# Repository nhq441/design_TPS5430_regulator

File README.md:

# TPS5430 Dual Buck Converter Module

---

## 📖 Introduction

This project presents the design and implementation of a **DC/DC Buck Converter (Step-Down) Power Supply Module** using **two Texas Instruments TPS5430** ICs. The module accepts a wide input voltage range of **14.4V – 25.2V** and delivers multiple regulated output rails suitable for embedded systems and microcontroller-based applications.

Key features include a **3-mode adjustable main output (VP)**, dual auxiliary LDO rails, a **Power Good LED indicator**, and a **configurable overcurrent protection** threshold set via a shunt resistor.

**Course:** Power Electronics and Applications — Course Code: `BTL_DTCSUD`

---

## 🖼️ PCB Images

### Schematic Overview
> 📷 *[Insert full schematic image here]*

---

### PCB Layout — Top Layer

---

### PCB Layout — Bottom Layer

---

### 3D Render

---

### Assembled Board
> 📷 *[Insert photo of the soldered/assembled board here]*

---

## ⚙️ Technical Specifications

| Parameter | Value | Notes |
| :--- | :--- | :--- |
| **Input Voltage ($V_{IN}$)** | 14.4V – 25.2V | Recommended operating range |
| **Main Output VP** | **5V / 12V / 3.3–12V** | 3 selectable modes |
| **VP Output Current** | Max **3A** | High-efficiency switching mode |
| **Auxiliary Output 1** | **5V** | Via LDO, for logic circuits |
| **Auxiliary Output 2** | **3.3V** | Via LDO, for MCUs (ESP32, STM32, etc.) |
| **Switching Frequency** | 500 kHz | Fixed internal oscillator |
| **Buck IC** | 2× TPS5430 | Texas Instruments |
| **Overcurrent Protection** | Configurable | Set via shunt resistor value |
| **Power Good Indicator** | LED (VP rail) | Signals stable output on VP |

---

## 🛠️ Design Details

### 1. Dual TPS5430 Architecture

The module employs **two independent TPS5430 ICs**:
- **IC1:** Drives the main output rail **VP**, supporting 3 selectable voltage modes.
- **IC2:** *(Describe the role of the second IC here — e.g., secondary rail, redundancy, or higher current capacity)*

### 2. Three-Mode Main Output (VP)

The VP rail supports three operating modes, selected via a switch or jumper:

| Mode | Output Voltage | Configuration |
| :---: | :---: | :--- |
| **Mode 1** | **5V** | Fixed feedback resistor network |
| **Mode 2** | **12V** | Fixed feedback resistor network |
| **Mode 3** | **3.3V – 12V** | Adjustable via potentiometer |

### 3. Feedback Network Calculation

The output voltage is set by a resistor divider ($R_1$, $R_2$) connected to the **VSENSE** pin, based on the internal reference $V_{ref} = 1.221V$:

$$V_{OUT} = V_{ref} \times \left(1 + \frac{R_1}{R_2}\right)$$

**With $R_1 = 10k\Omega$ (fixed):**

- **5V Mode:**

$$R_2 = \frac{R_1 \times V_{ref}}{V_{OUT} - V_{ref}} = \frac{10000 \times 1.221}{5.0 - 1.221} \approx 3.24k\Omega$$

- **12V Mode:**

$$R_2 = \frac{10000 \times 1.221}{12.0 - 1.221} \approx 1.13k\Omega$$

- **Variable Mode:** $R_2$ is replaced with a **5kΩ potentiometer in series with a 1kΩ fixed resistor**, allowing continuous adjustment from **3.3V to 12V**.

### 4. Auxiliary LDO Outputs (5V & 3.3V)

Both LDO regulators are cascaded from the **5V Buck output**, not directly from $V_{IN}$:
- **Reason:** Reduces the voltage drop across each LDO, minimizing power dissipation ($P_D = \Delta V \times I_{load}$).
- **Benefit:** Allows the use of compact packages (e.g., SOT-223) without thermal issues.

### 5. Power Good LED Indicator

A **Power Good LED** is connected to the VP rail. The LED lights up when VP reaches its target voltage, confirming stable regulation before connecting a load.

### 6. Configurable Overcurrent Protection

A **low-side shunt resistor** sets the overcurrent trip threshold. Changing the resistor value adjusts the protection level to match the target application's requirements. The sensing node is labeled **ISENSE** in the schematic.

---

## 📂 Project Structure

```text
BTL_DTCSUD/
├── docs/                       # Documentation & Report files
│   └── ...
├── Kicad/                      # Hardware Design Files
│   └── Buck_TPS5430/
│       ├── *.kicad_sch         # Schematic file
│       ├── *.kicad_pcb         # PCB Layout file
│       └── ...
├── reference/                  # Datasheets & Assignment requirements
│   └── ...
├── .gitignore
├── GIT_GUIDE
└── README.md
```

---

## 🚀 Getting Started

### Prerequisites
- **[KiCad EDA](https://www.kicad.org/)** — Version 9.0 or higher recommended
- **[Git](https://git-scm.com/)** — For version control

### Installation

**Option 1: Clone via Git (Recommended)**
```bash
git clone https://github.com/nhq441/design_TPS5430_regulator.git
```

**Option 2: Download ZIP**
1. Click the green **<> Code** button at the top right of this repository page.
2. Select **Download ZIP**.
3. Extract the `.zip` file to your working directory.

### Opening the Project
1. Launch **KiCad**.
2. Navigate to: `Kicad/Buck_TPS5430/`
3. Open: `Buck_TPS5430.kicad_pro`

---

## 🤝 Contributing

This project follows the **Gitflow Workflow**:

- **`main`**: Stable, verified designs only.
- **`develop`**: Primary integration branch for ongoing work.
- **`feature/*`**: Individual feature branches (e.g., `feature/Schematic`, `feature/PCB-Layout`).
  - Always branch from `develop` and merge back via Pull Request.

---

## 📄 License

This project is developed for **educational purposes** within the scope of the **Power Electronics and Applications** course.

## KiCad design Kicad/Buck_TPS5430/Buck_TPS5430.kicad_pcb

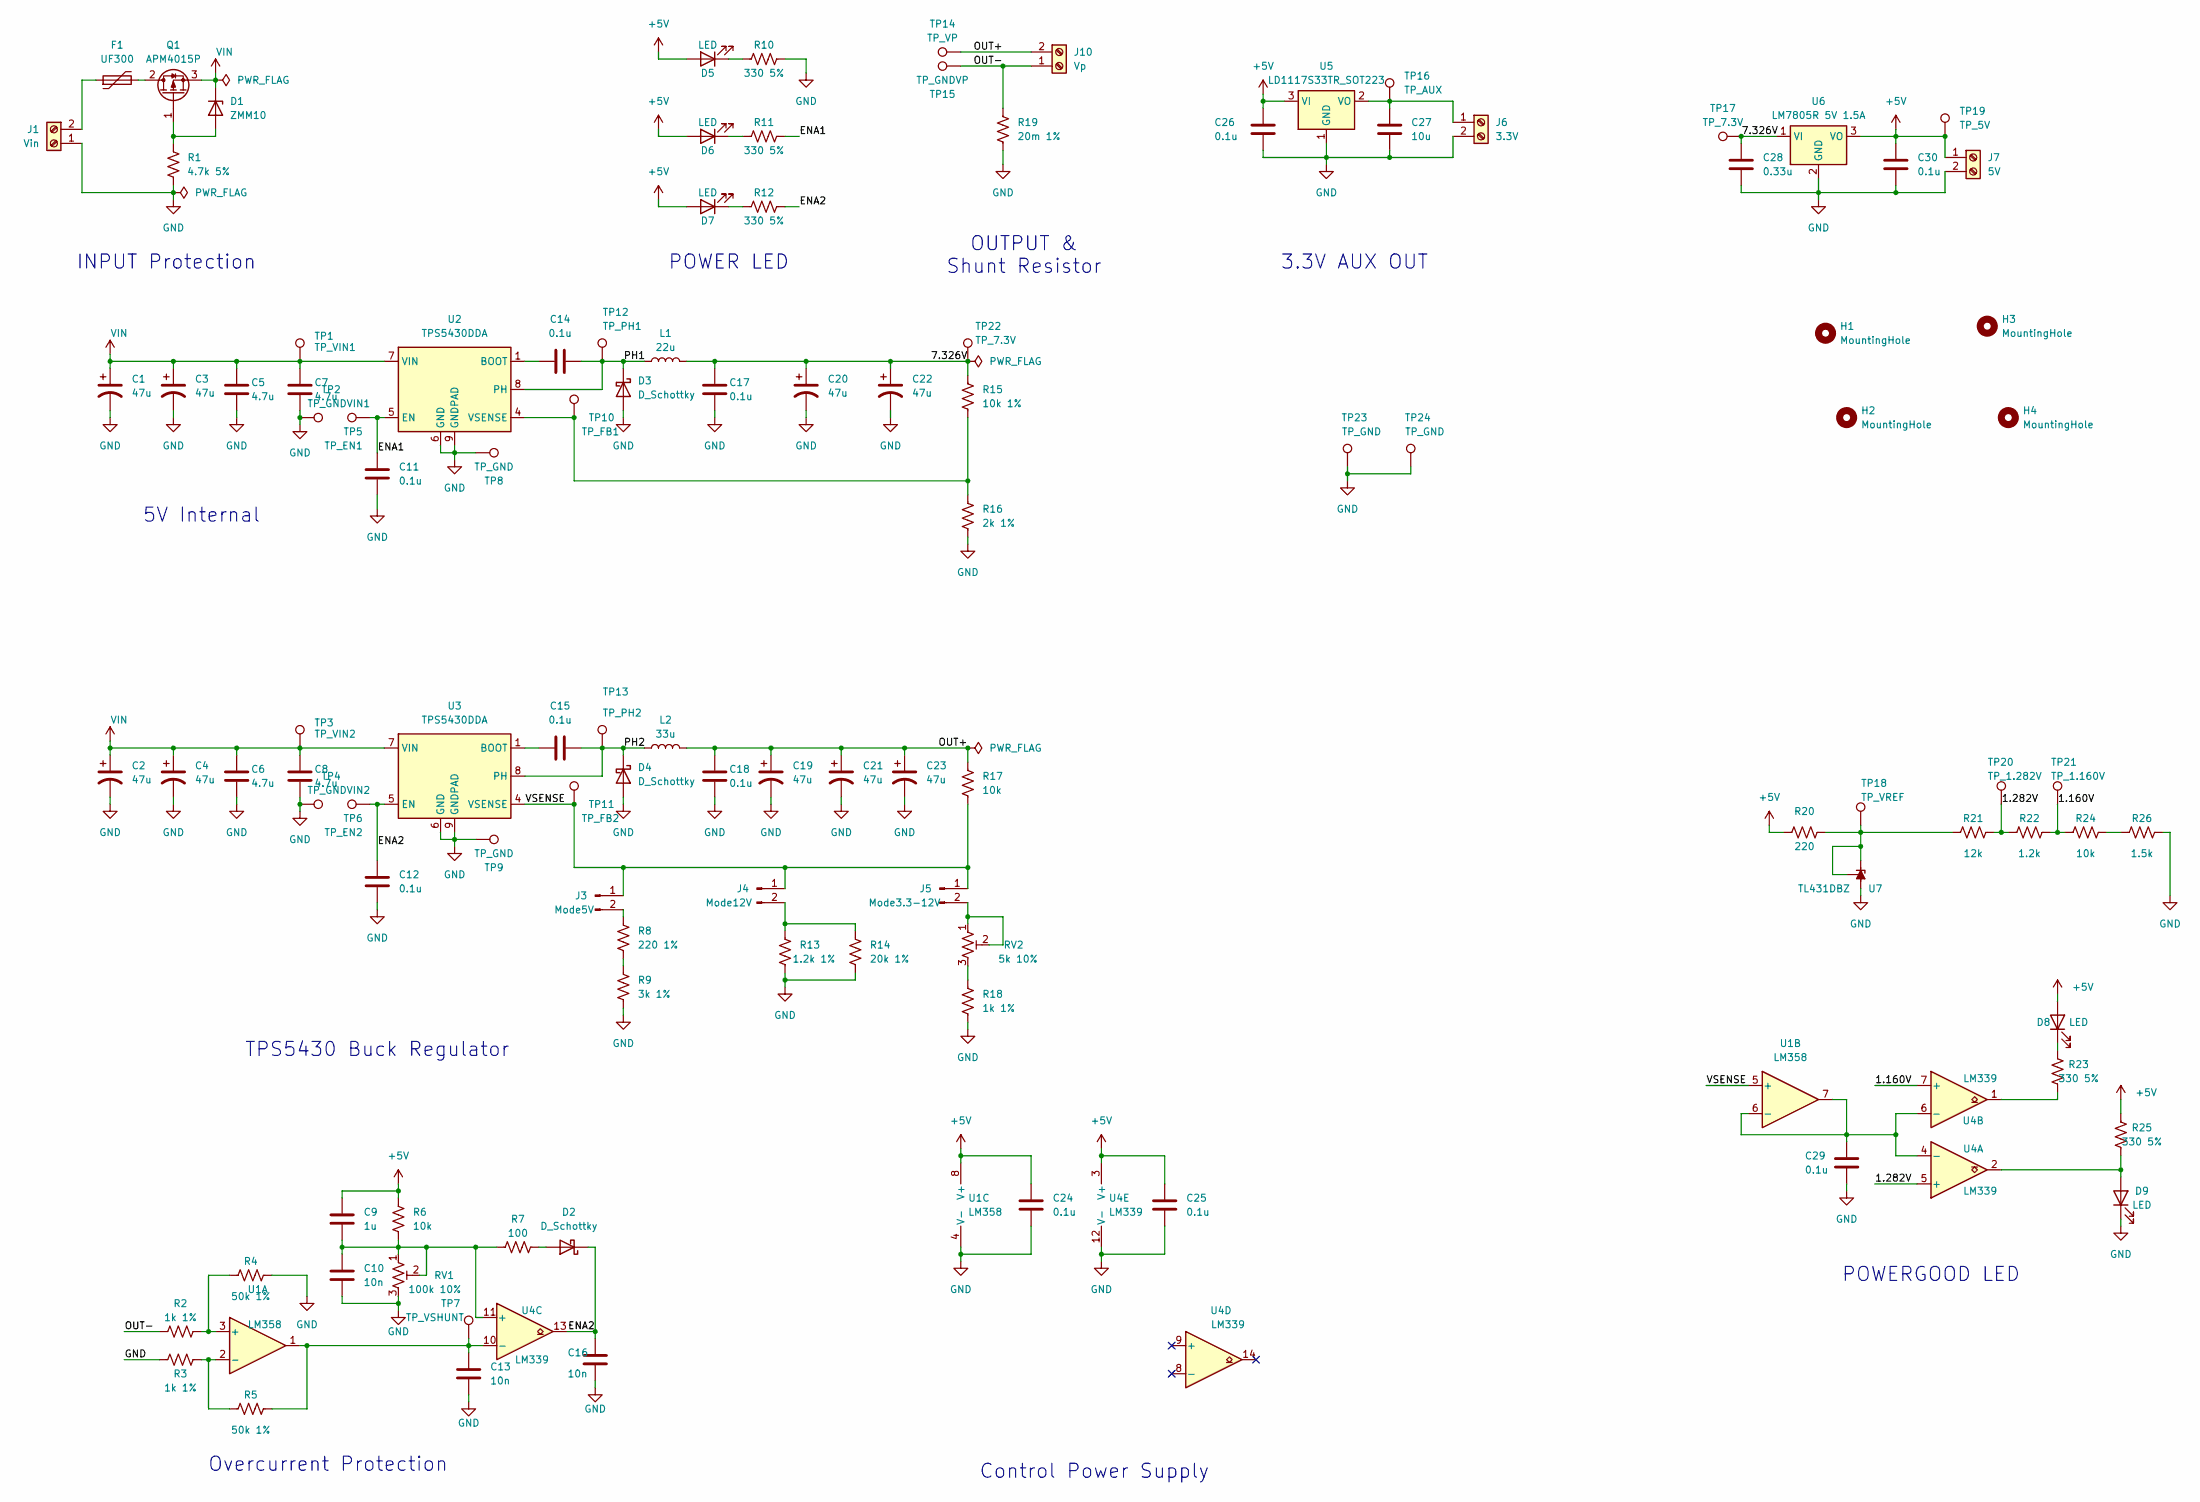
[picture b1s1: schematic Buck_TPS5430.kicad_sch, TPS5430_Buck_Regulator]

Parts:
C1, C2, C3, C4, C19, C20, C21, C22, C23: 47u; CP_Elec_6.3x7.7
C5, C6, C7, C8: 4.7u; C_0805_2012Metric_Pad1.18x1.45mm_HandSolder
C9: 1u; C_0805_2012Metric_Pad1.18x1.45mm_HandSolder
C10, C13, C16: 10n; C_0805_2012Metric_Pad1.18x1.45mm_HandSolder
C11, C12, C14, C15, C17, C18, C24, C25, C26, C29, C30: 0.1u; C_0805_2012Metric_Pad1.18x1.45mm_HandSolder
C27: 10u; C_0805_2012Metric_Pad1.18x1.45mm_HandSolder
C28: 0.33u; C_0805_2012Metric_Pad1.18x1.45mm_HandSolder
D1: ZMM10; D_MiniMELF
D2, D3, D4: D_Schottky; D_SMC
D5, D6, D7, D8, D9: LED; LED_0805_2012Metric_Pad1.15x1.40mm_HandSolder
F1: UF300; C_Disc_D11.0mm_W5.0mm_P5.00mm
H1, H2, H3, H4: MountingHole; MountingHole_3.2mm_M3
J1: Vin; TerminalBlock_Phoenix_MKDS-1,5-2-5.08_1x02_P5.08mm_Horizont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
J3: Mode5V; PinHeader_1x02_P2.54mm_Vertical
J4: Mode12V; PinHeader_1x02_P2.54mm_Vertical
J5: Mode3.3-12V; PinHeader_1x02_P2.54mm_Vertical
J6: 3.3V; TerminalBlock_Phoenix_MKDS-1,5-2-5.08_1x02_P5.08mm_Horizont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
J7: 5V; TerminalBlock_Phoenix_MKDS-1,5-2-5.08_1x02_P5.08mm_Horizont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
J10: Vp; TerminalBlock_Phoenix_MKDS-1,5-2-5.08_1x02_P5.08mm_Horizont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
L1: 22u; L_Coilcraft_MSS1038-XXX
L2: 33u; L_Coilcraft_MSS1278-XXX
Q1: APM4015P; TO-252-2
R1: 4.7k 5%; R_0805_2012Metric_Pad1.20x1.40mm_HandSolder
R2, R3, R18: 1k 1%; R_0805_2012Metric_Pad1.20x1.40mm_HandSolder
R4, R5: 50k 1%; R_0805_2012Metric_Pad1.20x1.40mm_HandSolder
R6, R17, R24: 10k; R_0805_2012Metric_Pad1.20x1.40mm_HandSolder
R7: 100; R_0805_2012Metric_Pad1.20x1.40mm_HandSolder
R8: 220 1%; R_0805_2012Metric_Pad1.20x1.40mm_HandSolder
R9: 3k 1%; R_0805_2012Metric_Pad1.20x1.40mm_HandSolder
R10, R11, R12, R23, R25: 330 5%; R_0805_2012Metric_Pad1.20x1.40mm_HandSolder
R13: 1.2k 1%; R_0805_2012Metric_Pad1.20x1.40mm_HandSolder
R14: 20k 1%; R_0805_2012Metric_Pad1.20x1.40mm_HandSolder
R15: 10k 1%; R_0805_2012Metric_Pad1.20x1.40mm_HandSolder
R16: 2k 1%; R_0805_2012Metric_Pad1.20x1.40mm_HandSolder
R19: 20m 1%; R_2512_6332Metric_Pad1.40x3.35mm_HandSolder
R20: 220; R_0805_2012Metric_Pad1.20x1.40mm_HandSolder
R21: 12k; R_0805_2012Metric_Pad1.20x1.40mm_HandSolder
R22: 1.2k; R_0805_2012Metric_Pad1.20x1.40mm_HandSolder
R26: 1.5k; R_0805_2012Metric_Pad1.20x1.40mm_HandSolder
RV1: 100k 10%; Potentiometer_Bourns_3296W_Vertical
RV2: 5k 10%; Potentiometer_Bourns_3296W_Vertical
TP1: TP_VIN1; TestPoint_Pad_D1.0mm
TP2: TP_GNDVIN1; TestPoint_Pad_D1.0mm
TP3: TP_VIN2; TestPoint_Pad_D1.0mm
TP4: TP_GNDVIN2; TestPoint_Pad_D1.0mm
TP5: TP_EN1; TestPoint_Pad_D1.0mm
TP6: TP_EN2; TestPoint_Pad_D1.0mm
TP7: TP_VSHUNT; TestPoint_Pad_D1.0mm
TP8, TP9, TP23, TP24: TP_GND; TestPoint_Pad_D1.0mm
TP10: TP_FB1; TestPoint_Pad_D1.0mm
TP11: TP_FB2; TestPoint_Pad_D1.0mm
TP12: TP_PH1; TestPoint_Pad_D1.0mm
TP13: TP_PH2; TestPoint_Pad_D1.0mm
TP14: TP_VP; TestPoint_Pad_D1.0mm
TP15: TP_GNDVP; TestPoint_Pad_D1.0mm
TP16: TP_AUX; TestPoint_Pad_D1.0mm
TP17, TP22: TP_7.3V; TestPoint_Pad_D1.0mm
TP18: TP_VREF; TestPoint_Pad_D1.0mm
TP19: TP_5V; TestPoint_Pad_D1.0mm
TP20: TP_1.282V; TestPoint_Pad_D1.0mm
TP21: TP_1.160V; TestPoint_Pad_D1.0mm
U1: LM358; SOIC-8_3.9x4.9mm_P1.27mm
U2, U3: TPS5430DDA; TI_SO-PowerPAD-8_ThermalVias
U4: LM339; SOIC-14_3.9x8.7mm_P1.27mm
U5: LD1117S33TR_SOT223; SOT-223-3_TabPin2
U6: LM7805R 5V 1.5A; TO-263-3_TabPin2
U7: TL431DBZ; SOT-23

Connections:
+5V: C9.1, C24.1, C25.1, C26.2, C30.1, D5.2 (A), D6.2 (A), D7.2 (A), D8.2 (A), J7.1, R6.2, R20.1, R25.2, TP19.1, U1.8 (V+), U4.3 (V+), U5.3 (VI), U6.3 (VO)
/1.160V: R22.2, R24.1, TP21.1, U4.7 (+)
/1.282V: R21.2, R22.1, TP20.1, U4.5 (+)
/7.326V: C17.1, C20.1, C22.1, C28.1, L1.2, R15.1, TP17.1, TP22.1, U6.1 (VI)
/ENA1: C11.1, R11.1, TP5.1, U2.5 (EN)
/ENA2: C12.1, C16.1, D2.1 (K), R12.1, TP6.1, U3.5 (EN), U4.13
/OUT+: C18.1, C19.1, C21.1, C23.1, J10.2 (Pin_1), L2.2, R17.1, TP14.1
/OUT-: J10.1 (Pin_2), R2.1, R19.1, TP15.1
/PH1: C14.2, D3.1 (K), L1.1, TP12.1, U2.8 (PH)
/PH2: C15.2, D4.1 (K), L2.1, TP13.1, U3.8 (PH)
/VSENSE: J3.1, J4.1, J5.1, R17.2, TP11.1, U1.5 (+), U3.4 (VSENSE)
GND: C1.2, C2.2, C3.2, C4.2, C5.2, C6.2, C7.2, C8.2, C10.2, C11.2, C12.2, C13.2, C16.2, C17.2, C18.2, C19.2, C20.2, C21.2, C22.2, C23.2, C24.2, C25.2, C26.1, C27.1, C28.2, C29.1, C30.2, D3.2 (A), D4.2 (A), D9.1 (K), J1.1 (Pin_2), J6.2, J7.2, R1.2, R3.1, R4.2, R9.2, R10.1, R13.2, R14.2, R16.1, R18.1, R19.2, R26.2, RV1.3, TP2.1, TP4.1, TP8.1, TP9.1, TP23.1, TP24.1, U1.4 (V-), U2.6 (GND), U2.9 (GNDPAD), U3.6 (GND), U3.9 (GNDPAD), U4.12 (V-), U5.1 (GND), U6.2 (GND), U7.3 (A)
unnamed: D1.2 (A), Q1.1 (G), R1.1
unnamed: D2.2 (A), R7.1
unnamed: D5.1 (K), R10.2
unnamed: D6.1 (K), R11.2
unnamed: D7.1 (K), R12.2
unnamed: D8.1 (K), R23.2
unnamed: D9.2 (A), R25.1, U4.2
unnamed: F1.1, J1.2 (Pin_1)
unnamed: J3.2, R8.1
unnamed: J4.2, R13.1, R14.1
unnamed: J5.2, RV2.1, RV2.2
unnamed: C27.2, J6.1, TP16.1, U5.2 (VO)
unnamed: F1.2, Q1.2 (D)
unnamed: R8.2, R9.1
unnamed: R18.2, RV2.3
unnamed: R23.1, U4.1
unnamed: R24.2, R26.1
unnamed: R2.2, R4.1, U1.3 (+)
unnamed: R3.2, R5.1, U1.2 (-)
unnamed: C29.2, U1.6 (-), U1.7, U4.4 (-), U4.6 (-)
unnamed: C14.1, U2.1 (BOOT)
unnamed: R15.2, R16.2, TP10.1, U2.4 (VSENSE)
unnamed: C15.1, U3.1 (BOOT)
unnamed: C9.2, C10.1, R6.1, R7.2, RV1.1, RV1.2, U4.11 (+)
unnamed: C13.1, R5.2, TP7.1, U1.1, U4.10 (-)
unnamed: R20.2, R21.1, TP18.1, U7.1 (K), U7.2 (REF)
VIN: C1.1, C2.1, C3.1, C4.1, C5.1, C6.1, C7.1, C8.1, D1.1 (K), Q1.3 (S), TP1.1, TP3.1, U2.7 (VIN), U3.7 (VIN)

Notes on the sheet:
TPS5430 Buck Regulator
OUTPUT & Shunt Resistor
POWER LED
3.3V AUX OUT
Overcurrent Protection
POWERGOOD LED
Control Power Supply
5V Internal
INPUT Protection

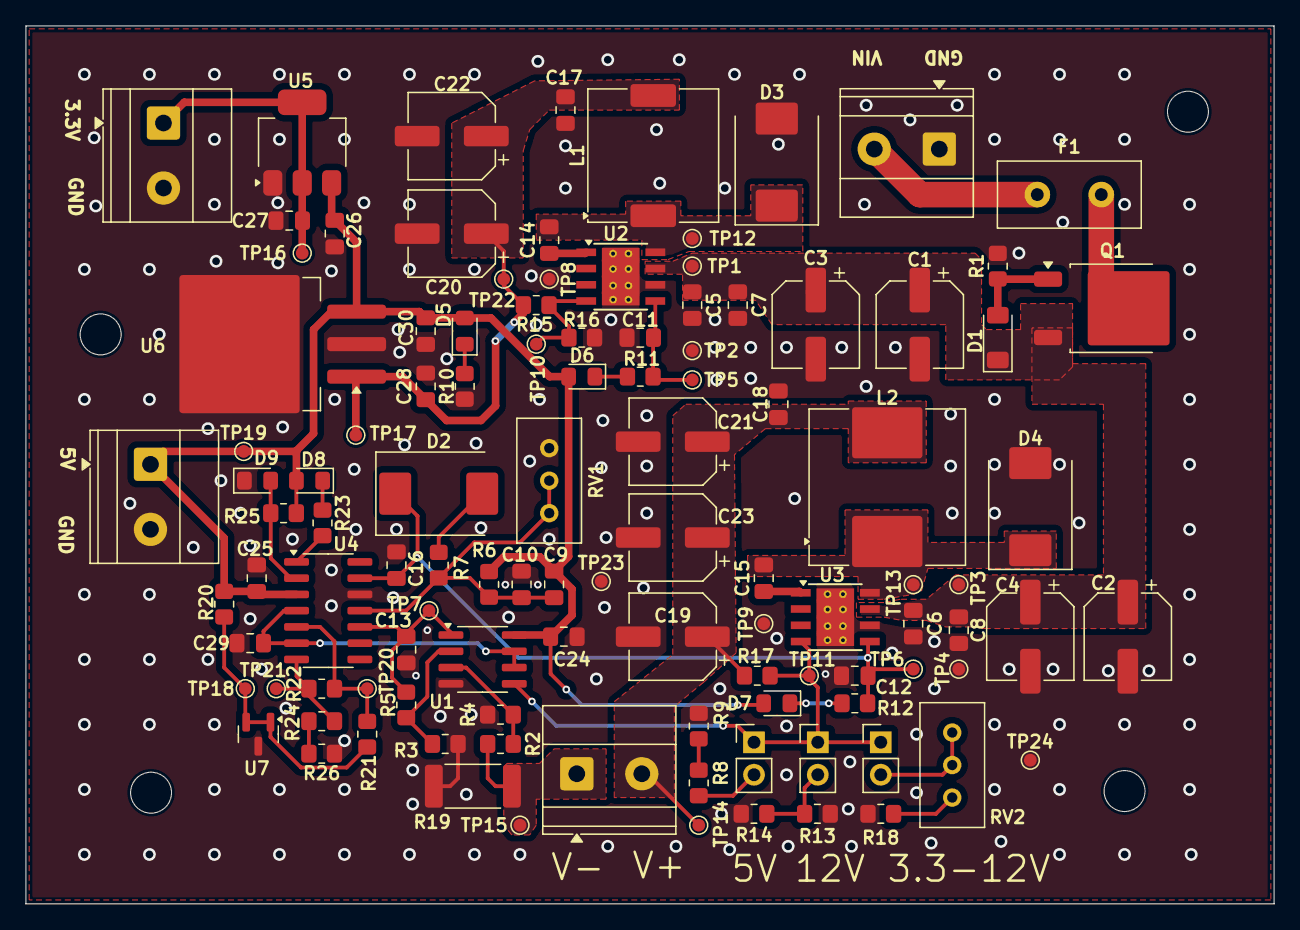
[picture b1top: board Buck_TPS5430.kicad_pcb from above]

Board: 2 copper layers, 97.5 x 68.6 mm, 113 parts (0 on the bottom side), 39 nets.

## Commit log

2026-02-05 first commit: creat project
2026-02-05 docs:upload file doc & reference
2026-02-05 chore: edit .gitignore file
2026-02-05 feat: draw basic schematic tps543s
2026-02-06 Revise README for TPS5430 Buck Converter Module
    Updated project details and specifications in README.
2026-02-11 WIP: add capacitor and powergood led
2026-02-12 WIP: compelete powergood led and add short current protection
2026-02-12 Creat PCB branch
2026-02-12 Chore: edit doc guide
2026-02-14 feat: finish schematic topology (values TBD - to be determined)
2026-02-15 feat: add git guide file
2026-02-15 Cập nhật tài liệu hướng dẫn Git cho dự án TPS5430
    Cập nhật hướng dẫn sử dụng Git cho dự án TPS5430, bao gồm các khái niệm cơ bản, quy trình làm việc và các lệnh Git thường dùng.
2026-02-15 Add GIT_GUIDE to project structure in README
2026-03-07 ref: add reference document
2026-03-07 feat: add 5v buck, edit logic of power led, calculate R, L, C
2026-03-12 feat:PCB layout
2026-03-13 feat: COMPLETE PCB Layout

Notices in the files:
README.md:
License: Educational
